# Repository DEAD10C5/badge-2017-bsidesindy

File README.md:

## BSidesIndy 2017 Badge

We did this as a workshop during @indybsides in March 2017.

See the wiki for more information.

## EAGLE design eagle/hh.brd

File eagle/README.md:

###
https://learn.sparkfun.com/tutorials/using-eagle-schematic

### push buttons
 https://www.sparkfun.com/products/97

I have ordered a bunch of this push buttons. These push buttons fit easily into a breadboard. However, now that I have my prototype working and I am making a schematic in Eagle, I have no idea what the dimensions are to make my switch component in Eagle. It is very frustrating and time wasting.
 M-Short / about 2 years ago /  1
This switch is actually in our Eagle libraries. Check under the Electromagnetic/Switch-Momentary-2 section. It should be the first one (Description: Omron switch). Or internal part number is SWCH-8441, as long as you have that one selected you should be good. Feel free to email techsupport if you have any other questions or ever need more information.

### esp-8266

* Clone the repo :

https://github.com/nodemcu/nodemcu-devkit-v1.0

Copy the file ESP12E_DEVKIT.lbr from the repo to the folder /Applications/EAGLE-7.5.0/lbr

Open the brd file, click "Library" then "use"

### OLED SSD-1306

http://learn.acrobotic.com/tutorials/post/esp8266-oled-display-using-i2c

### resistors (using internal instead)

http://electronics.stackexchange.com/questions/65015/resistor-and-capacitor-package-types-eagle-cad

Resistors with different power ratings have different standard sizes (for example, 1/8W vs 1/4W). Likewise for capacitors, the part you need to use depends on the type of capacitor (monolithic, ceramic, electrolytic, etc) and the capacitance and voltage ratings. Assuming you are looking at the RCL library, 0207/10 simply means the body of the resistor is 2mm x 7mm and the hole to hole spacing is 10mm. Similarly C050-035x075 means 5mm hole spacing, 3.5mm x 7.5mm outline. You have to figure out (with calipers, for example) if this will work with the parts you are planning to use.

http://www.instructables.com/id/Draw-Electronic-Schematics-with-CadSoft-EAGLE/step5/Add-resistors/

### battery holder

https://www.sparkfun.com/products/13113
Note: This part can be found in the Electromechanical Eagle library under ‘Battery18650’.

### some notes

One thing you can do is print the board layout at 1:1 scale on paper before sending it out to the fab to see if the parts fit. You can catch common errors this way.

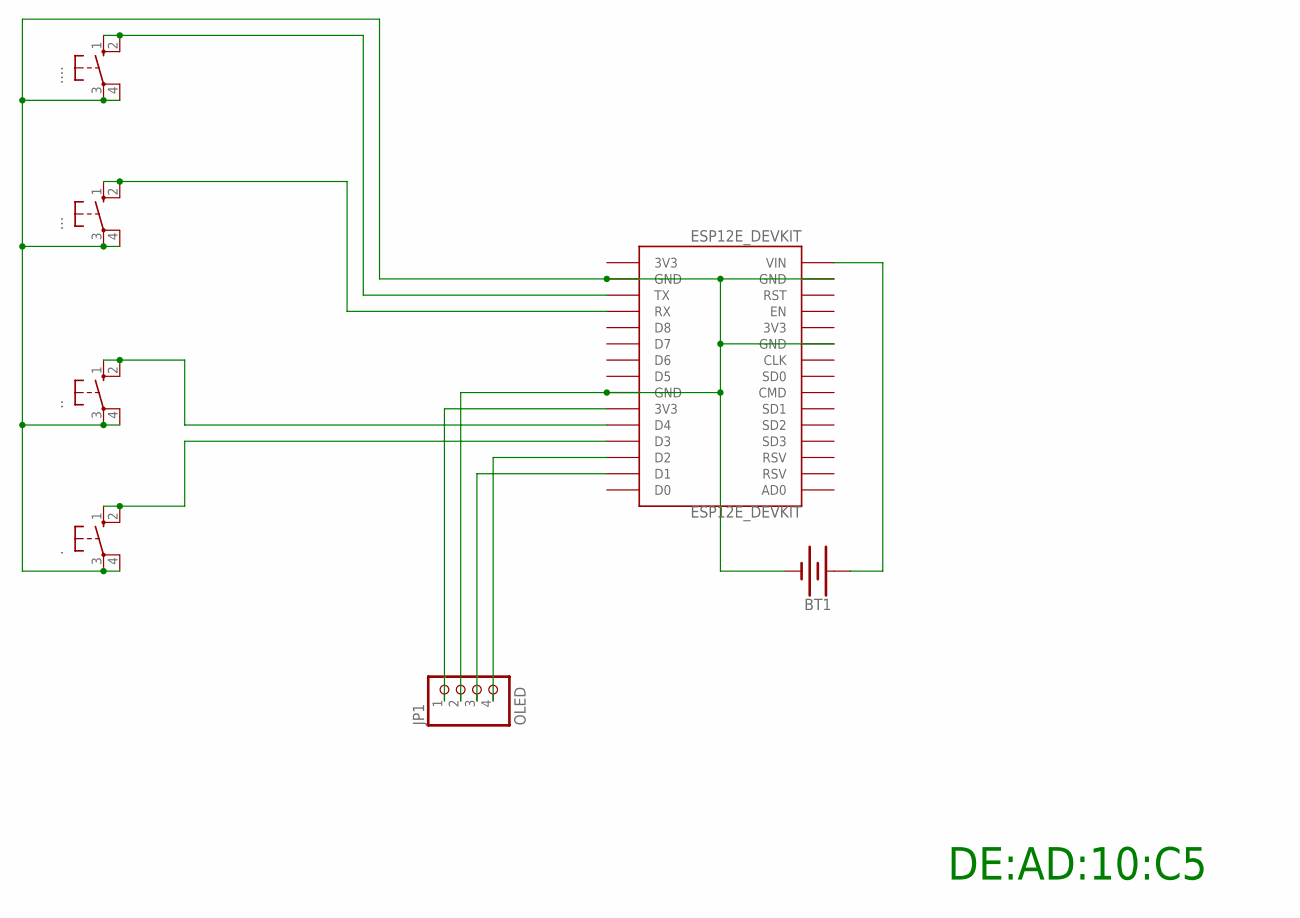
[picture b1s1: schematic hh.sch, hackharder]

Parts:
., .., ..., ....: 10-XX; B3F-10XX
BT1: BATTERY-18650; BATTERY_18650-HOLDER
ESP12E_DEVKIT: ESP12E_DEVKIT
JP1: OLED; 1X04

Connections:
unnamed: ..3, ..4 (P1), ...3, ...4 (P1), ....3, ....4 (P1), .....3, .....4 (P1), BT1.GND@1 (-), ESP12E_DEVKIT.GND@0 (GND), ESP12E_DEVKIT.GND@1 (GND), ESP12E_DEVKIT.GND@2 (GND), ESP12E_DEVKIT.GND@3 (GND), JP1.2
unnamed: ..1 (S), ..2 (S1), ESP12E_DEVKIT.D3
unnamed: ESP12E_DEVKIT.3V3@1 (3V3), JP1.1
unnamed: BT1.PWR@1 (+), ESP12E_DEVKIT.VIN
unnamed: ESP12E_DEVKIT.D1, JP1.3
unnamed: ESP12E_DEVKIT.D2, JP1.4
unnamed: ...1 (S), ...2 (S1), ESP12E_DEVKIT.D4
unnamed: ....1 (S), ....2 (S1), ESP12E_DEVKIT.RX
unnamed: .....1 (S), .....2 (S1), ESP12E_DEVKIT.TX

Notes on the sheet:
DE:AD:10:C5

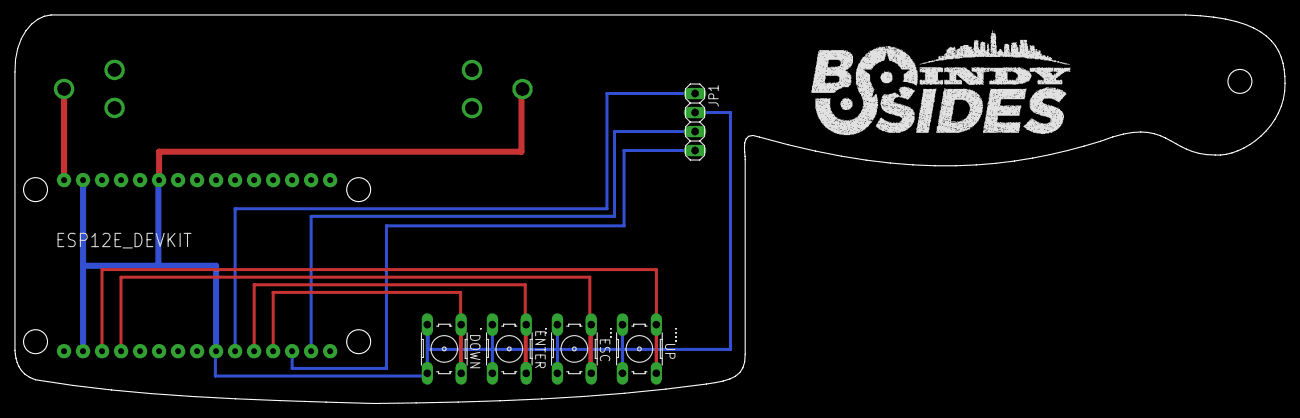
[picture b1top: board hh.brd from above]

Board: 2 copper layers, 169.7 x 51.9 mm, 7 parts (1 on the bottom side), 9 nets.

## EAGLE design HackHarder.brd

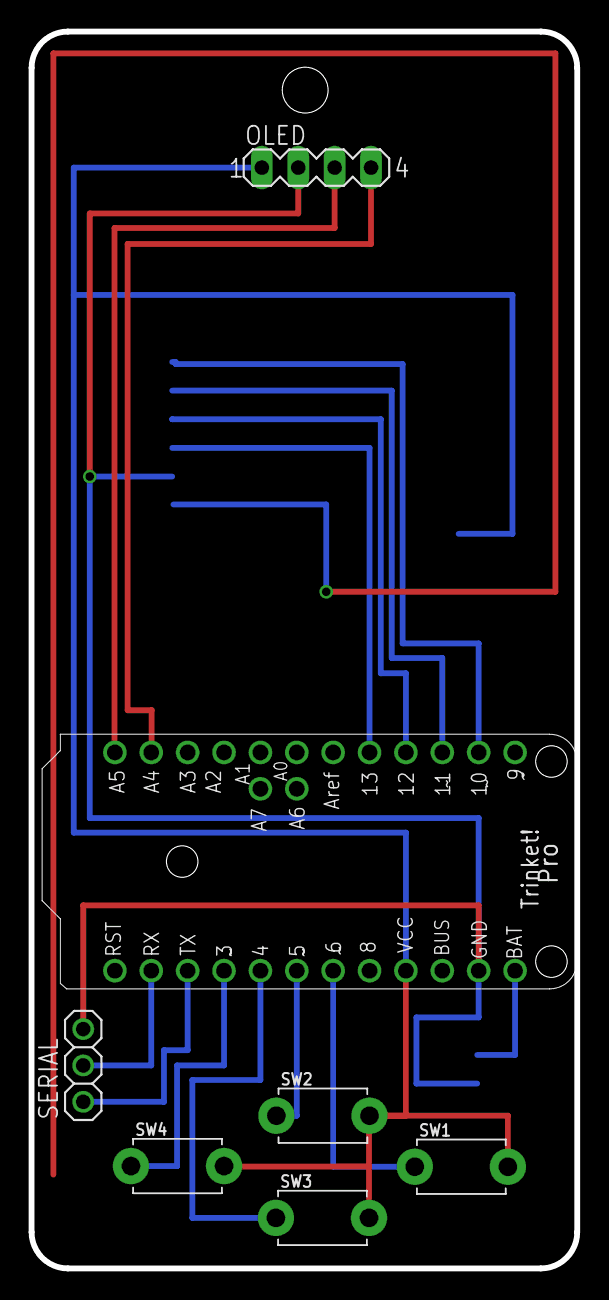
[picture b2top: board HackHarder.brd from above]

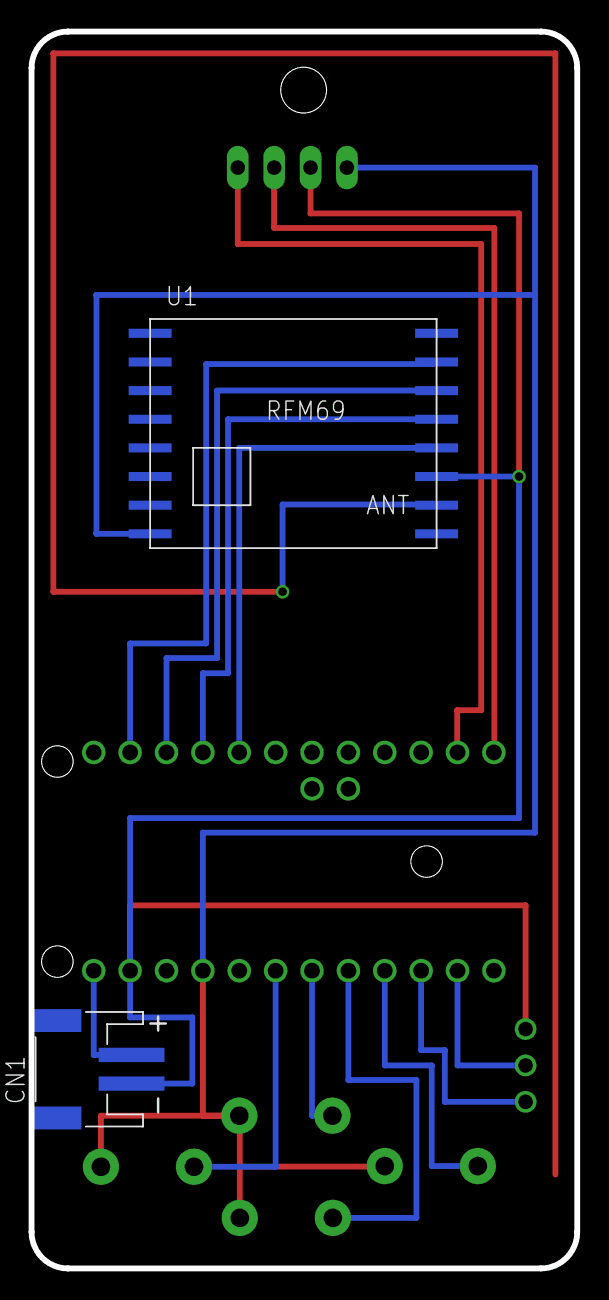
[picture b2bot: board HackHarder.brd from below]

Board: 2 copper layers, 38.1 x 86.4 mm, 9 parts (2 on the bottom side), 15 nets.

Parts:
CN1: JST-PH-2-SMT-RA
MCU1: PRO_TRINKET; PROTRINKET
OLED: MA04-1
SERIAL: 1X03
SW1, SW2, SW3, SW4: TACT_PANA-EVQ
U1: RFM69HW; RFM69_PADS

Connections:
G$1: CN1.2, MCU1.GND, OLED.2, SERIAL.3, U1.GND
unnamed: CN1.1, MCU1.BAT+
unnamed: MCU1.A5, OLED.3
unnamed: MCU1.A4, OLED.4
unnamed: MCU1.11, U1.MOSI
unnamed: MCU1.12, U1.MISO
unnamed: MCU1.13, U1.SCK
unnamed: MCU1.10, U1.NSS
unnamed: MCU1.6, SW1.P$1
unnamed: MCU1.5, SW2.P$1
unnamed: MCU1.4, SW3.P$1
unnamed: MCU1.3, SW4.P$1
unnamed: MCU1.TX, SERIAL.1
unnamed: MCU1.RX, SERIAL.2
VCC: MCU1.VCC, OLED.1, SW1.P$2, SW2.P$2, SW3.P$2, SW4.P$2, U1.VCC

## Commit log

2016-08-17 Badge Files
    Initial Eagle Badge Files
2016-08-30 Add files via upload
    Updated board with smaller footprint
2016-08-31 Add files via upload
    Latest version
2016-08-31 Add files via upload
    Now with serial breakout! I'm not sure that the footprint for the radio is correct - need to double-check the pintout on the module spec sheet...
2016-12-10 badge pcb art
2016-12-10 minor updates
2016-12-17 pcb updates
2016-12-28 graphics updates
2017-01-05 Created new SVG with simplified vectors and outline
2017-01-05 Created outline and silkscreen artwork, imported both to kicad and created board
2017-01-08 cleanup
2017-01-08 eagle schematic
2017-01-23 adding lua stuff
2017-01-25 Update PartsList.md
    added batteries, make a table
2017-01-25 Update PartsList.md
    fix table
2017-01-25 add optional parts
2017-02-09 change source of ESP8266 for shorter ordering time
2017-02-27 Update PartsList.md
    added micro USB cable
2017-03-01 add sample arduino code
2017-03-02 prototyping updates
2017-03-03 refactoring, added first button
2017-03-03 tweak
2017-03-05 button test sketch
2017-03-10 Updated instructions for OS X
2017-03-10 Fixed typos in readme
2017-03-13 updates to eagle files
2017-03-16 design updates
2017-03-17 Update README.md
    added battery holder info
2017-03-17 images and brd update
2017-03-17 revise component placement in eagle
2017-03-17 add silkscreen text in eagle
2017-03-17 wiring 1
2017-03-17 wiring 2
2017-03-17 adding OSH park drc for reference
2017-03-17 fix eagle drc error
2017-03-18 testing final design
2017-03-18 tweaks
2017-03-18 arduino sketch cleanup
2017-03-18 Added battery clips, fixed VIN, moved switches closer together to accommodate the battery clips, added a ground plane under the radio.
2017-03-18 Update PartsList.md
    changed battery holder
2017-03-18 Update README.md
    change battery holder
2017-03-19 Add files via upload
    Latest Update
2017-03-19 gerber files
2017-03-19 Update PartsList.md
    change OLED source, must have Vcc pin on far left
2017-03-19 Create LICENSE
2017-03-19 silkscreen updates
2017-03-19 silkscreen placement
2017-03-19 Major changes to placement of components
2017-03-19 Trace Revisions
2017-03-19 silkscreen edits
2017-03-19 Artwork
    Added BSides Indy artwork
2017-03-19 Modified switch labels
2017-04-03 Added WiFi Scanning code
2017-04-03 Code Update
    Allows you to scan for WiFi networks, scroll through the networks
    (UP/DOWN buttons), re-scan networks (ESC button), and connect to a
    network with open authentication (ENTER button)
2017-04-03 Better WiFi error handling
    Better WiFi error handling
2017-04-04 Allow to disconnect after WiFi is connected
    Pressing ESC during or after WiFi connection will re-scan and allow you
    to connect to another network.
2017-06-09 Latest Updates
2018-04-04 cleanup first release
2022-08-24 Add .whitesource configuration file
2022-10-08 Add .whitesource configuration file (#4)
2022-10-08 convert eagle to KiCAD
2022-10-08 convert eagle to KiCAD (#5)
2022-10-08 add kibot action
2022-10-08 add kibot action (#6)
    * add kibot action
    * add kibot action
    * add kibot action
2022-10-08 add kibot action (#7)
2023-12-15 Add renovate.json

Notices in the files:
parts and their libraries:
SF_Batteries: Licensing: Creative Commons ShareAlike 4.0 International - https://creativecommons.org/licenses/by-sa/4.0
